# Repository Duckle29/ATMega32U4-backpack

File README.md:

This is a small backpack PCB, meant to go with some 2.4" I2C OLED LCD. It exposes ALL pins on the ATMega32U4, so can be used for pretty much anything.

## Pinout:

| Pin | Encoder |  UART  |   I2C  | WS2812 |    SPI   |        CS3V3        |
|:---:|:-------:|:------:|:------:|:------:|:--------:|:-------------------:|
|  1  |   GND   |   GND  |   GND  |   GND  |   MISO   | 3V3 shifted IO (B0) |
|  2  |    B    | TX-3V3 |   5V   |  Data  |    3V3   |                     |
|  3  |    A    |   RX   | SCL-5V |   5V   |  SCK-3V3 |                     |
|  4  |    SW   |  5V in | SDA-5V |        | MOSI-3V3 |                     |
|  5  |         |        |        |        |   Reset  |                     |
|  6  |         |        |        |        |    GND   |                     |

The remaining pins are broken out on the back, with their port and number listed.

On the bottom is a micro-B USB.

**R4 and R5**  
Are I2C pullups. Attach these only if no other I2C device has pullups on them already.

**R6 and R7**  
Are optional pull-ups for the encoder. These can help if you have a noisy signal due to the weak internal pullups of the IC.

**Power**  
If the board is powered through the USB, the 5v power limit is 100mA, as it passes through D1. This is done to enable the chip to test if it's powered through USB or not.

```C
bool has_usb(void) {
  /* return (UDADDR & _BV(ADDEN)); */
   USBCON |= (1 << OTGPADE); // enables VBUS pad
   _delay_us(5);
   return (USBSTA & (1<<VBUS));  // checks state of VBUS
}
```

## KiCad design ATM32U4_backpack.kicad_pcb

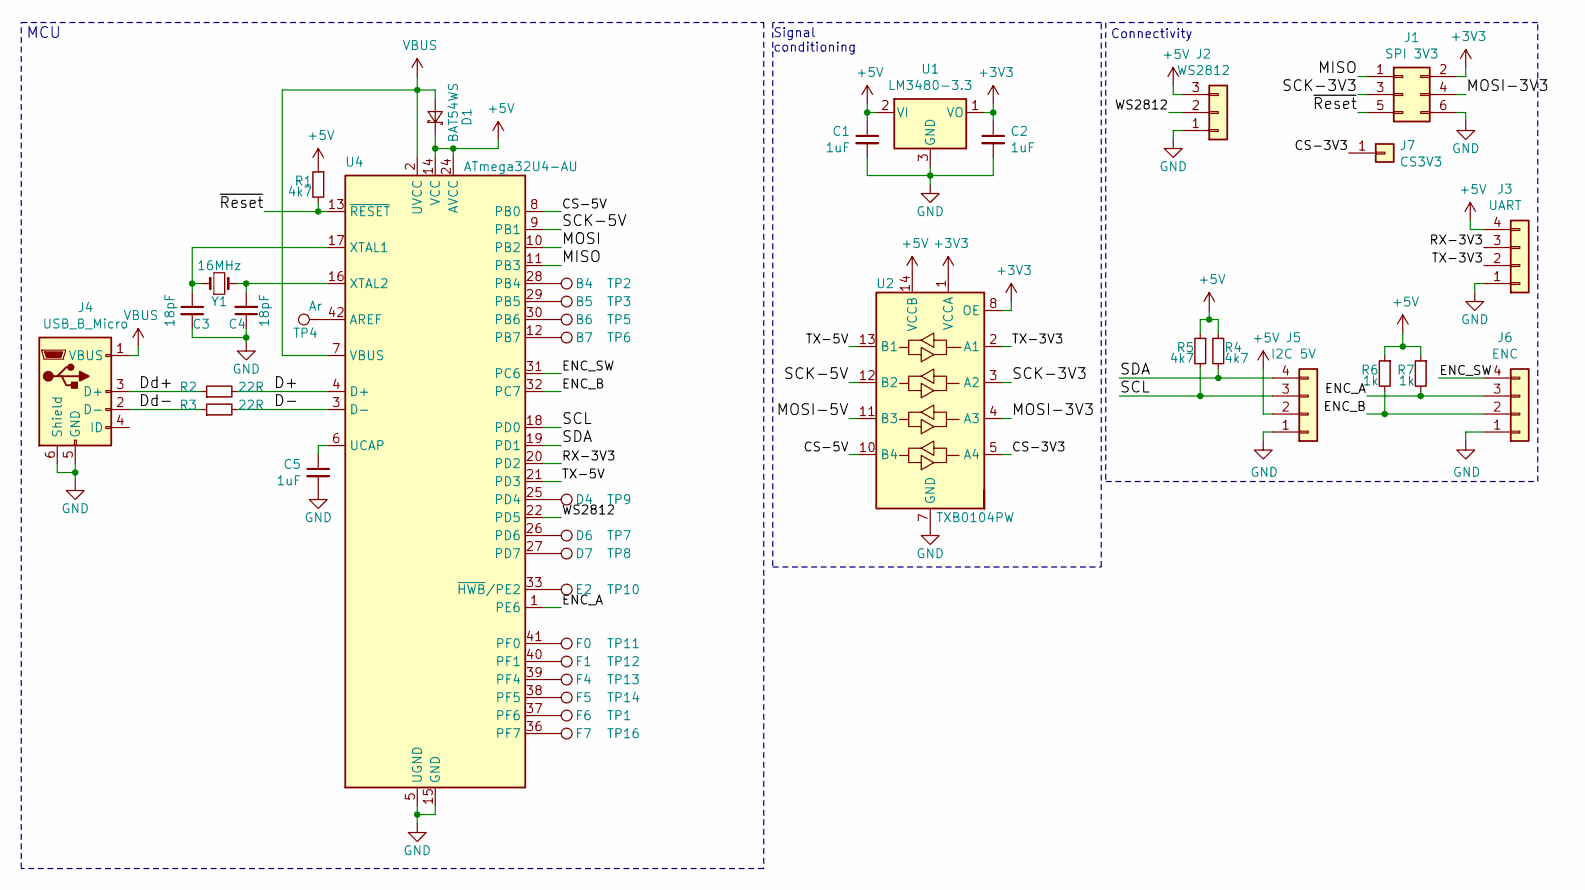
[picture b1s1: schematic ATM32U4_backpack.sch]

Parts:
C1, C2, C5: 1uF; C_0603_1608Metric
C3, C4: 18pF; C_0603_1608Metric
D1: BAT54WS; D_SOD-323_HandSoldering
J1: SPI 3V3; PinHeader_2x03_P2.54mm_Horizontal
J2: WS2812; PinHeader_1x03_P2.54mm_Horizontal
J3: UART; PinHeader_1x04_P2.54mm_Horizontal
J4: USB_B_Micro; USB_Micro-B_Molex_47346-0001
J5: I2C 5V; PinHeader_1x04_P2.54mm_Horizontal
J6: ENC; PinHeader_1x04_P2.54mm_Horizontal
J7: CS3V3; PinHeader_1x01_P2.54mm_Horizontal
R1, R4, R5: 4k7; R_0603_1608Metric
R2, R3: 22R; R_0603_1608Metric
R6, R7: 1k; R_0603_1608Metric
TP1: F6; TestPoint_Pad_1.0x1.0mm
TP2: B4; TestPoint_Pad_1.0x1.0mm
TP3: B5; TestPoint_Pad_1.0x1.0mm
TP4: Ar; TestPoint_Pad_1.0x1.0mm
TP5: B6; TestPoint_Pad_1.0x1.0mm
TP6: B7; TestPoint_Pad_1.0x1.0mm
TP7: D6; TestPoint_Pad_1.0x1.0mm
TP8: D7; TestPoint_Pad_1.0x1.0mm
TP9: D4; TestPoint_Pad_1.0x1.0mm
TP10: E2; TestPoint_Pad_1.0x1.0mm
TP11: F0; TestPoint_Pad_1.0x1.0mm
TP12: F1; TestPoint_Pad_1.0x1.0mm
TP13: F4; TestPoint_Pad_1.0x1.0mm
TP14: F5; TestPoint_Pad_1.0x1.0mm
TP16: F7; TestPoint_Pad_1.0x1.0mm
U1: LM3480-3.3; SOT-23
U2: TXB0104PW; TSSOP-14_4.4x5mm_P0.65mm
U4: ATmega32U4-AU; TQFP-44_10x10mm_P0.8mm
Y1: 16MHz; Crystal_SMD_5032-2Pin_5.0x3.2mm_HandSoldering

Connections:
+3V3: C2.1, J1.2, U1.1 (VO), U2.1 (VCCA), U2.8 (OE)
+5V: C1.1, D1.1 (K), J2.3, J3.4, J5.2, R1.1, R4.1, R5.1, R6.1, R7.1, U1.2 (VI), U2.14 (VCCB), U4.14 (VCC), U4.24 (AVCC), U4.34 (VCC), U4.44 (AVCC)
/CS-3V3: J7.1, U2.5 (A4)
/CS-5V: U2.10 (B4), U4.8 (PB0)
/D+: R2.2, U4.4 (D+)
/D-: R3.2, U4.3 (D-)
/Dd+: J4.3 (D+), R2.1
/Dd-: J4.2 (D-), R3.1
/ENC_A: J6.3, R7.2, U4.1 (PE6)
/ENC_B: J6.2, R6.2, U4.32 (PC7)
/ENC_SW: J6.4, U4.31 (PC6)
/MISO: J1.1, U4.11 (PB3)
/MOSI-3V3: J1.4, U2.4 (A3)
/RX-3V3: J3.3, U4.20 (PD2)
/SCK-3V3: J1.3, U2.3 (A2)
/SCK-5V: U2.12 (B2), U4.9 (PB1)
/SCL: J5.3, R5.2, U4.18 (PD0)
/SDA: J5.4, R4.2, U4.19 (PD1)
/TX-3V3: J3.2, U2.2 (A1)
/TX-5V: U2.13 (B1), U4.21 (PD3)
/WS2812: J2.2, U4.22 (PD5)
/~Reset: J1.5, R1.2, U4.13 (~RESET)
GND: C1.2, C2.2, C3.2, C4.1, C5.2, J1.6, J2.1, J3.1, J4.5 (GND), J4.6 (Shield), J5.1, J6.1, U1.3 (GND), U2.7 (GND), U4.5 (UGND), U4.15 (GND), U4.23 (GND), U4.35 (GND), U4.43 (GND)
unnamed: C3.1, U4.17 (XTAL1), Y1.1
unnamed: C4.2, U4.16 (XTAL2), Y1.2
unnamed: C5.1, U4.6 (UCAP)
unnamed: TP1.1, U4.37 (PF6)
unnamed: TP2.1, U4.28 (PB4)
unnamed: TP3.1, U4.29 (PB5)
unnamed: TP4.1, U4.42 (AREF)
unnamed: TP5.1, U4.30 (PB6)
unnamed: TP6.1, U4.12 (PB7)
unnamed: TP7.1, U4.26 (PD6)
unnamed: TP8.1, U4.27 (PD7)
unnamed: TP9.1, U4.25 (PD4)
unnamed: TP10.1, U4.33 (~HWB~/PE2)
unnamed: TP11.1, U4.41 (PF0)
unnamed: TP12.1, U4.40 (PF1)
unnamed: TP13.1, U4.39 (PF4)
unnamed: TP14.1, U4.38 (PF5)
unnamed: TP16.1, U4.36 (PF7)
VBUS: D1.2 (A), J4.1 (VBUS), U4.2 (UVCC), U4.7 (VBUS)

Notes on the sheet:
MCU
Signal conditioning
Connectivity

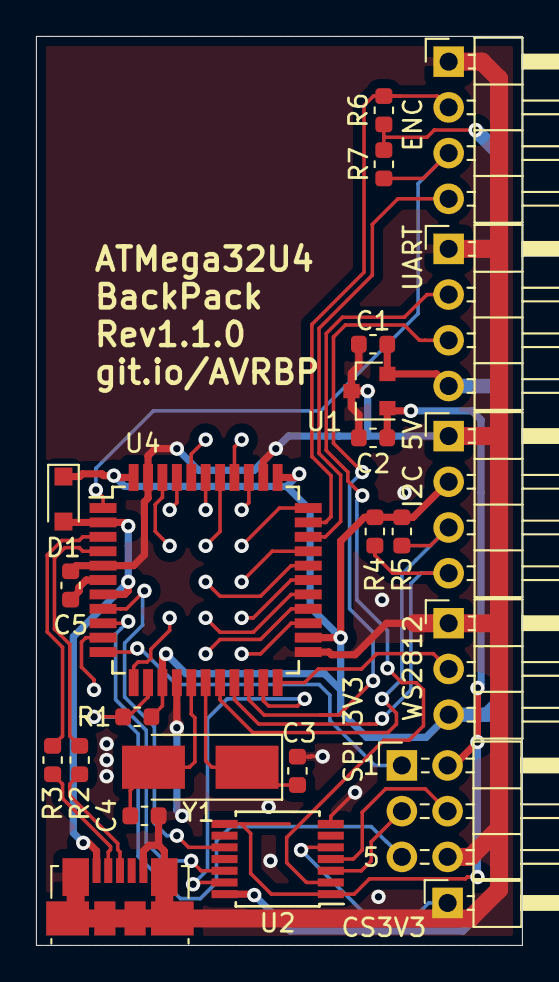
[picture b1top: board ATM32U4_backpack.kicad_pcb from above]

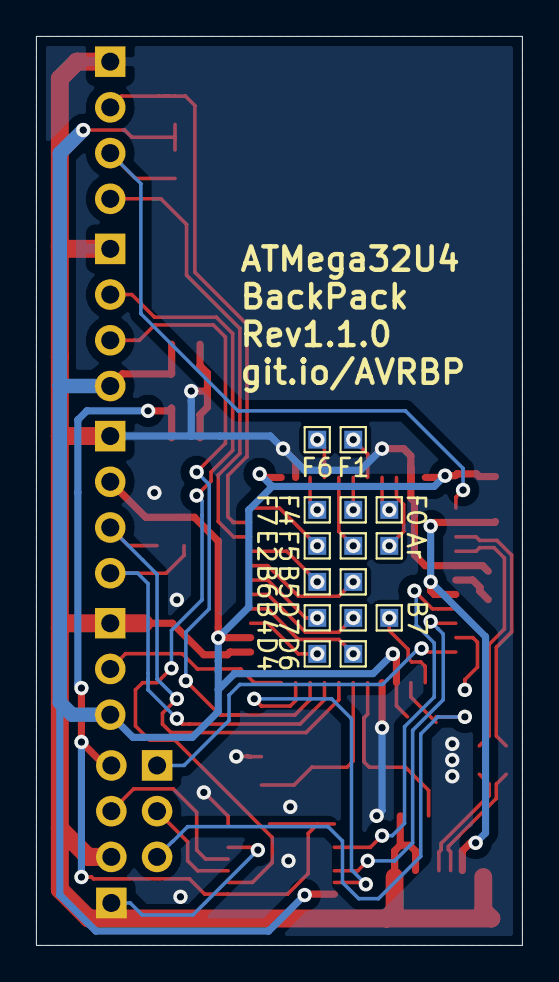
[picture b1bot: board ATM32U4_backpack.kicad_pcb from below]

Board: 2 copper layers, 27.0 x 50.5 mm, 39 parts (15 on the bottom side), 42 nets.

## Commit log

2019-07-10 Added License and expanded gitignore
2019-07-10 added schematic pdf and readme
2019-07-11 Added gerbers
2019-07-11 Fixed back silkscreen
2019-07-11 Made SPI level-shifted to 3v3
2019-07-11 Updated readme to reflect v1.1.0
2019-07-11 Added 3D model of crystal
2019-07-21 made the wiggly lines more pretty
